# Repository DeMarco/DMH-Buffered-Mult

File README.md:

# DMH-Buffered-Mult
Buffered Multiple module for the Navigator Modular System

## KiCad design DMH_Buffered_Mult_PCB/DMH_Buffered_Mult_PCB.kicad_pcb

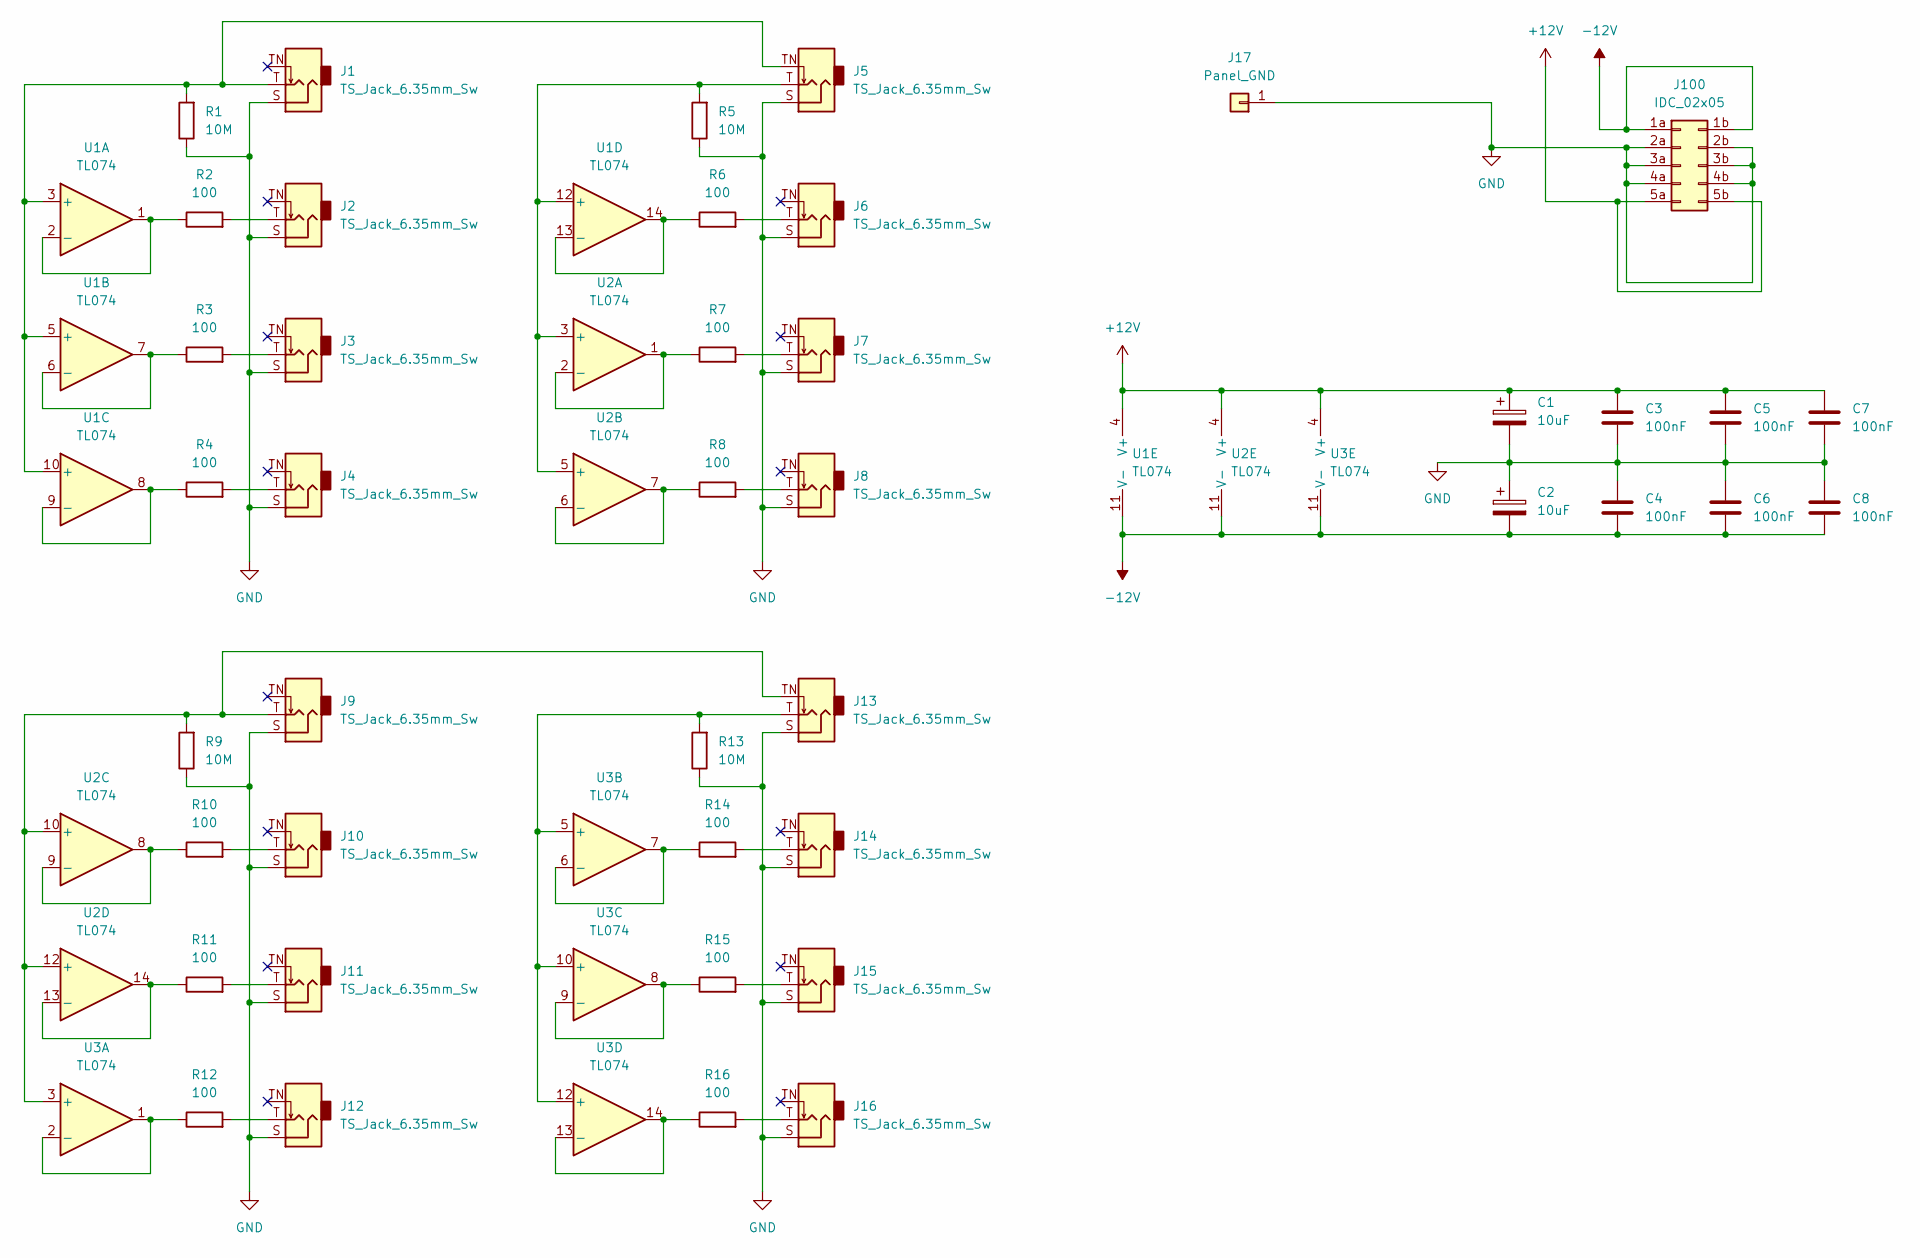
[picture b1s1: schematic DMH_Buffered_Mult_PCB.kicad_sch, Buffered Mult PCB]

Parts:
C1, C2: 10uF; CP_Radial_D4.0mm_P2.00mm
C3, C4, C5, C6, C7, C8: 100nF; C_Disc_D4.3mm_W1.9mm_P5.00mm
J1, J2, J3, J4, J5, J6, J7, J8, J9, J10, J11, J12, J13, J14, J15, J16: TS_Jack_6.35mm_Sw; CUI_MJ-63052A
J17: Panel_GND; PinHeader_1x01_P2.54mm_Vertical
J100: IDC_02x05; IDC-Header_2x05_P2.54mm_Vertical_Eurorack
R1, R5, R9, R13: 10M; R_Axial_DIN0207_L6.3mm_D2.5mm_P7.62mm_Horizontal
R2, R3, R4, R6, R7, R8, R10, R11, R12, R14, R15, R16: 100; R_Axial_DIN0207_L6.3mm_D2.5mm_P7.62mm_Horizontal
U1, U2, U3: TL074; DIP-14_W7.62mm_Socket

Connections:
+12V: C1.1, C3.1, C5.1, C7.1, J100.5a, J100.5b, U1.4 (V+), U2.4 (V+), U3.4 (V+)
-12V: C2.2, C4.2, C6.2, C8.2, J100.1a, J100.1b, U1.11 (V-), U2.11 (V-), U3.11 (V-)
GND: C1.2, C2.1, C3.2, C4.1, C5.2, C6.1, C7.2, C8.1, J1.S, J2.S, J3.S, J4.S, J5.S, J6.S, J7.S, J8.S, J9.S, J10.S, J11.S, J12.S, J13.S, J14.S, J15.S, J16.S, J17.1, J100.2a, J100.2b, J100.3a, J100.3b, J100.4a, J100.4b, R1.1, R5.1, R9.1, R13.1
unnamed: J2.T, R2.2
unnamed: J3.T, R3.2
unnamed: J4.T, R4.2
unnamed: J6.T, R6.2
unnamed: J7.T, R7.2
unnamed: J8.T, R8.2
unnamed: J10.T, R10.2
unnamed: J11.T, R11.2
unnamed: J12.T, R12.2
unnamed: J14.T, R14.2
unnamed: J15.T, R15.2
unnamed: J16.T, R16.2
unnamed: J1.T, J5.TN, R1.2, U1.3 (+), U1.5 (+), U1.10 (+)
unnamed: R2.1, U1.1, U1.2 (-)
unnamed: R3.1, U1.6 (-), U1.7
unnamed: R4.1, U1.8, U1.9 (-)
unnamed: J5.T, R5.2, U1.12 (+), U2.3 (+), U2.5 (+)
unnamed: R6.1, U1.13 (-), U1.14
unnamed: R7.1, U2.1, U2.2 (-)
unnamed: R8.1, U2.6 (-), U2.7
unnamed: J9.T, J13.TN, R9.2, U2.10 (+), U2.12 (+), U3.3 (+)
unnamed: R10.1, U2.8, U2.9 (-)
unnamed: R11.1, U2.13 (-), U2.14
unnamed: R12.1, U3.1, U3.2 (-)
unnamed: J13.T, R13.2, U3.5 (+), U3.10 (+), U3.12 (+)
unnamed: R14.1, U3.6 (-), U3.7
unnamed: R15.1, U3.8, U3.9 (-)
unnamed: R16.1, U3.13 (-), U3.14

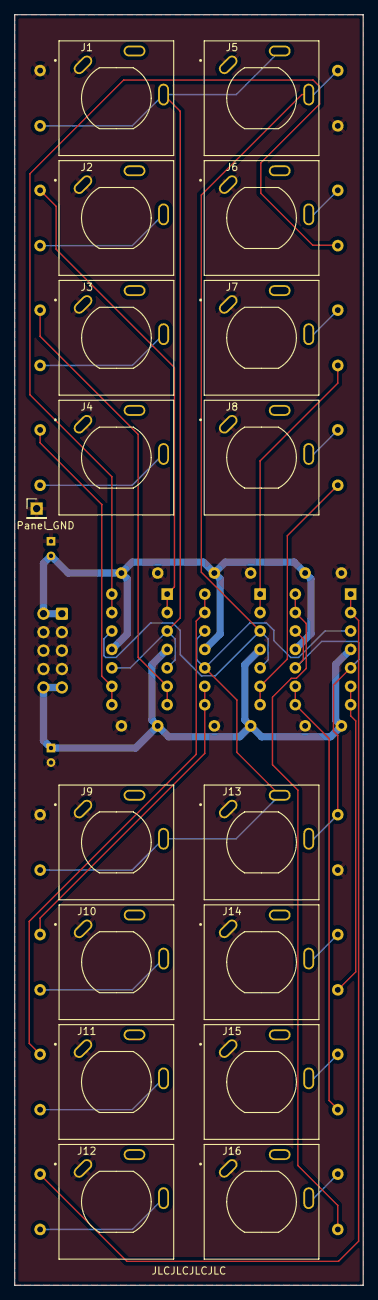
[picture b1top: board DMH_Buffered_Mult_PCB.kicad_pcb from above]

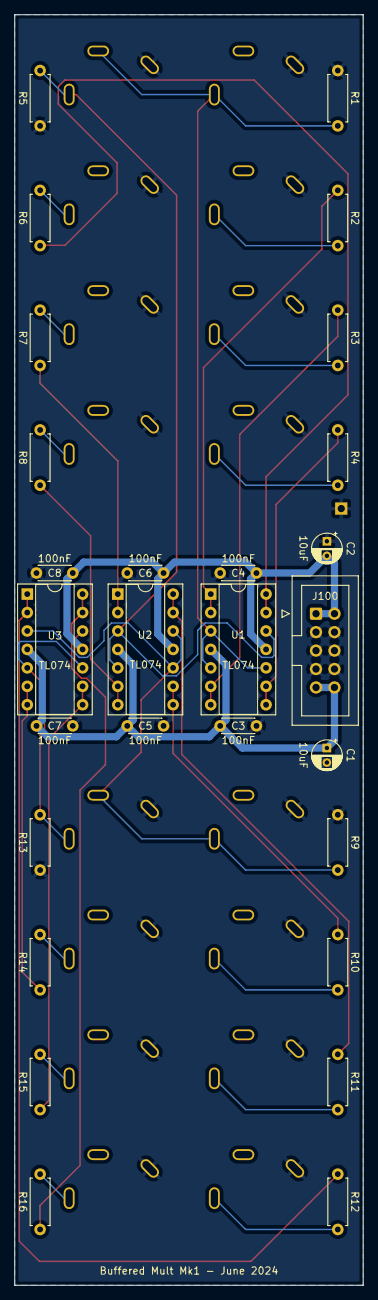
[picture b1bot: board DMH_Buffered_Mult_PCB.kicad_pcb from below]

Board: 2 copper layers, 48.0 x 175.0 mm, 45 parts (28 on the bottom side), 31 nets.

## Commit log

2024-06-27 Moved Buff Mult PCB to its own repo
2024-06-27 Moved Buff Mult Panel to its own repo
2024-06-27 Deleted submodule
2024-06-27 Added synth stuff sub module to PCB project
2024-06-27 Deleted submodule from PANEL project
2024-06-27 Added synth stuff submodule to PANEL project
2024-06-27 Font thickness?
2024-06-27 User Comments dot and comma?
2024-06-29 sync libs
2024-06-29 Generated Panel Gerbers
2024-06-29 Generated PCB gerbers
2024-06-29 Zipped gerbers
2024-07-02 Exported BoM
2024-07-13 Synced SynthStuff libs
2024-09-21 Copied board stackup configs from another board
